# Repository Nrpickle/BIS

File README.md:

BIS
===

A repo for my Bus Information System. 

This device will take the bus route information from the Corvallis (OR) transit system and output it on 7 segment displays. 

This project is my first experience with the ESP8266 $5 WiFi module.

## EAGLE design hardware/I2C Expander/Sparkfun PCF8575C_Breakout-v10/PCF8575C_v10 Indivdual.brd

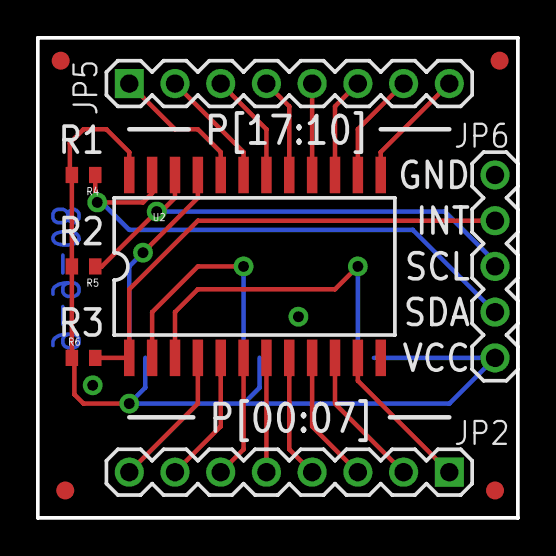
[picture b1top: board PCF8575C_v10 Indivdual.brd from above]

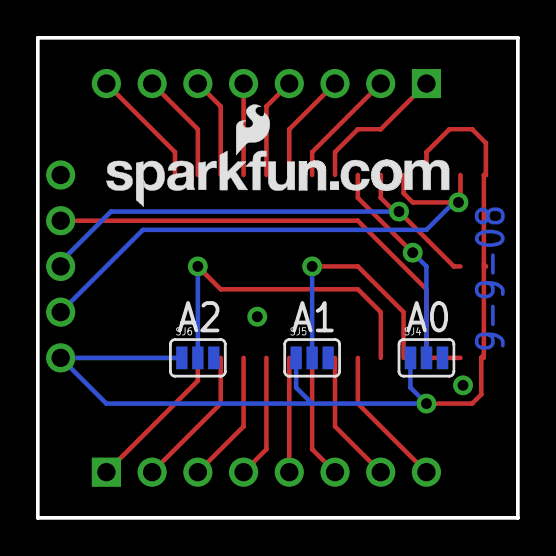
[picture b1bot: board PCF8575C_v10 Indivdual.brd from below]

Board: 2 copper layers, 26.7 x 26.7 mm, 15 parts (4 on the bottom side), 24 nets.

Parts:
E$5, E$6, E$7, E$8: FIDUCIAL-1X2
JP2, JP5: 1X08
JP6: 1X05
R4, R5, R6: C0402
SJ4: A0; SJ_3
SJ5: A1; SJ_3
SJ6: A2; SJ_3
U2: PCF8575C; SO-24DW
U$1: LOGO-SFENEW; SFE-NEW-WEBLOGO

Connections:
A3: SJ4.2, U2.21
A4: SJ5.2, U2.2
A5: SJ6.2, U2.3
GND1: JP6.1, SJ4.3, SJ5.3, SJ6.3, U2.12
INT1: JP6.2, R6.2, U2.1
P1: JP5.1, U2.20
P2: JP5.2, U2.19
P3: JP5.3, U2.18
P4: JP5.4, U2.17
P5: JP5.5, U2.16
P6: JP5.6, U2.15
P7: JP5.7, U2.14
P8: JP5.8, U2.13
PO8: JP2.8, U2.4
PO9: JP2.7, U2.5
PO10: JP2.5, U2.7
PO11: JP2.4, U2.8
PO12: JP2.3, U2.9
PO13: JP2.2, U2.10
PO14: JP2.1, U2.11
PO15: JP2.6, U2.6
SCL1: JP6.3, R5.1, U2.22
SDA1: JP6.4, R4.1, U2.23
VCC1: JP6.5, R4.2, R5.2, R6.1, SJ4.1, SJ5.1, SJ6.1, U2.24

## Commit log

2014-12-12 Added layout diagram
    Added diagram that describes the physical layout of the prototype
2014-12-12 Added PCF8575C Breakout Board files
2014-12-12 Added Documentation
2014-12-12 Added Pin Allocation Info
2014-12-13 Added I2C PCB Prototype Schematic
2014-12-13 Added I2C Break
2014-12-16 Clarified Documentation
2014-12-20 Updated PCB Prototype Schematic
    Added requirement for 220 ohm resistors
2014-12-20 Small Schematic Fix
2014-12-27 BIS Display PCBs Added
    Display Board schematic ported from TinyCAD into PADS and used to
    generate PCB layout file.
2014-12-27 PCF8575C Silkscreen Fixed
    IC outline appeared in PADS but not in generated Gerber.
2014-12-27 Decoupling Cap and Ground Plane Added
    Additions to help with high speed communication added.
2014-12-27 Resistors Added to Display Board
    Pullup and current limiting resistors have been added to the design.
2014-12-27 Resistor Number Reduced
    14 220 Ohm resistors reduced by placing them on common cathodes.
2014-12-27 Revert "Resistor Number Reduced"
    This reverts commit 881abcf642ee9551273dd546ed50deaea26de49b.
2014-12-27 PCF8575C Footprint Changed
    PCF8575CDBQ is non-stocked so the footprint has been changed to
    PCF8575CDB.
2014-12-27 Transistor Pin Issue Fixed
    Source and Drain were reversed in the part decal.
2015-01-10 Reorganized docs
2015-01-10 Added Initial Build Picture
2015-01-12 Added Access to Realtime ETAs Protocol
2015-01-13 Added TriMet Developer Resources
2015-01-17 Added Bare Minimum Disp Board Control
2015-01-17 Implemented Individual Number Control
2015-01-18 Display Board Enclosure SolidWorks Parts Added
    The first revision for the 3D printed display board enclosure.
2015-01-23 Added configureToWrite
2015-01-24 Added HW Requirements for Drive and Display
2015-01-24 Actually added HW Requirements
2015-01-24 Added Character (a-f) Functionality
2015-01-24 Added Display class, removed parse from realtime, added libraries
2015-01-24 Added Timer library
2015-01-24 Added note about dual nano-setup
2015-01-24 Added the I2C object to the struct, added error state to configureToWrite
2015-01-24 Added writeToDisplay member function
2015-01-24 Added setLeft and setRight, added uppercase protection to struct wrapper
2015-01-24 Made struct variables private
    Class, anyone?
2015-01-24 Added setAll
2015-01-24 Added TimerOne library
2015-01-24 Moved state machine switch to ISR
2015-01-24 Added "bis init" capability
2015-01-25 Added init sequence / ESP8266 test code (non-functional)
2015-01-27 Added ESP8266 Documentation / Serial Test Arduino Sketch
2015-01-27 Added development notes for ESP 8266
2015-01-27 Added HW Requirements for ESP 8266 Dev Board
2015-01-27 Changed dev notes
2015-01-27 Achieved communication with ESP8266!
2015-01-27 Connected to WiFi!
2015-01-27 Added documentation / HW Requirements
2015-01-27 Connected to Google [NickNet]
2015-01-27 Made LED indicate WiFi connectivity
2015-01-27 Changed HW Requirements to add LED to board
2015-01-27 [Not Working] Attempt to connect to CTS
2015-01-27 Implemented webpage pull (Not CTS)
    Used example code from http://www.cse.dmu.ac.uk/~sexton/ESP8266/
2015-01-27 Added HW Requirements - Indicator LEDs
2015-01-27 Changed HW Requirements
2015-01-30 Added data
2015-02-02 Added Drive Board Schematic
2015-02-02 Removed item from HW Req
2015-02-02 Updated Drive Board Schematic
2015-02-02 Changed HW Req
2015-02-02 Finalized Current Version of Drive Board Schematic
2015-02-02 Added second version of Display Board
2015-02-02 Updated v.2 of Display Board Schematic
2015-02-02 Exported image of schematic
2015-02-02 Added pngs of Sheets
2015-02-02 Added initial Dev Board Schematic
2015-02-02 Added gitignore and gitattributes
2015-02-02 Updated ESP Dev Board Schematic
2015-02-02 Changed Drive Board Schematic
2015-02-03 Added Current ESP Development Code
2015-02-03 [Not Working] Changed Server/Page Request
    This has not been tested, looking to revert back to a previous version
2015-02-03 fix conflicts
2015-02-03 Arg, fix conflicts
2015-02-03 Implemented Software Serial ESP
2015-02-24 [Not Working] Added Reset Feature
2018-03-24 Added PDF of display board
